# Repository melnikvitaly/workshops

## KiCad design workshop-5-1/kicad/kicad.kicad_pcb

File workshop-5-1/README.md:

# Workshop 5-1 — ESP32-S3 Dev Board

## 1. Task — Schematic of power supply

Design the power supply for the board: USB-C input, Li-Ion charging, battery
input, and a regulated 3.3 V rail for the ESP32-S3 module.

### Power chain

| Stage | Part | Function |
|-------|------|----------|
| USB-C input | `USB1` USB4105-GF-A-120 + `D4` 1N5819HW-7-F | 5 V bus input with reverse-current Schottky |
| Charger | `U5` BQ24040DSQR | Li-Ion linear charger, 5 V → `VBAT` |
| Battery | `CN1` XH-2AW | Single-cell Li-Ion connector on `VBAT` |
| Switch | `SW3` JS102011SAQN | Power switch on `VBAT` |
| Regulator | `U6` TLV75801PDBVR | Adjustable LDO, `VBAT` → `VCC` |

The LDO output is set by the `R9` / `R10` feedback divider. With
V<sub>FB</sub> = 0.55 V (TLV758P datasheet, eq. 2):

```
VOUT = VFB × (1 + R9 / R10) = 0.55 V × (1 + 255k / 51k) = 3.3 V
```

Charger programming and indication: `R7` (1 k) sets the fast-charge current,
`R6` (1 k) the pre-termination threshold, `R12` (10 k) the TS thermistor
branch. `LED1` shows charging (`CHG`), `LED2` shows USB power present (`PG`),
`LED3` shows the regulated rail is live.

### Schematic

Source file: [kicad/.history/kicad.kicad_sch](kicad/.history/kicad.kicad_sch)
(KiCad project: [kicad/kicad.kicad_pro](kicad/kicad.kicad_pro))

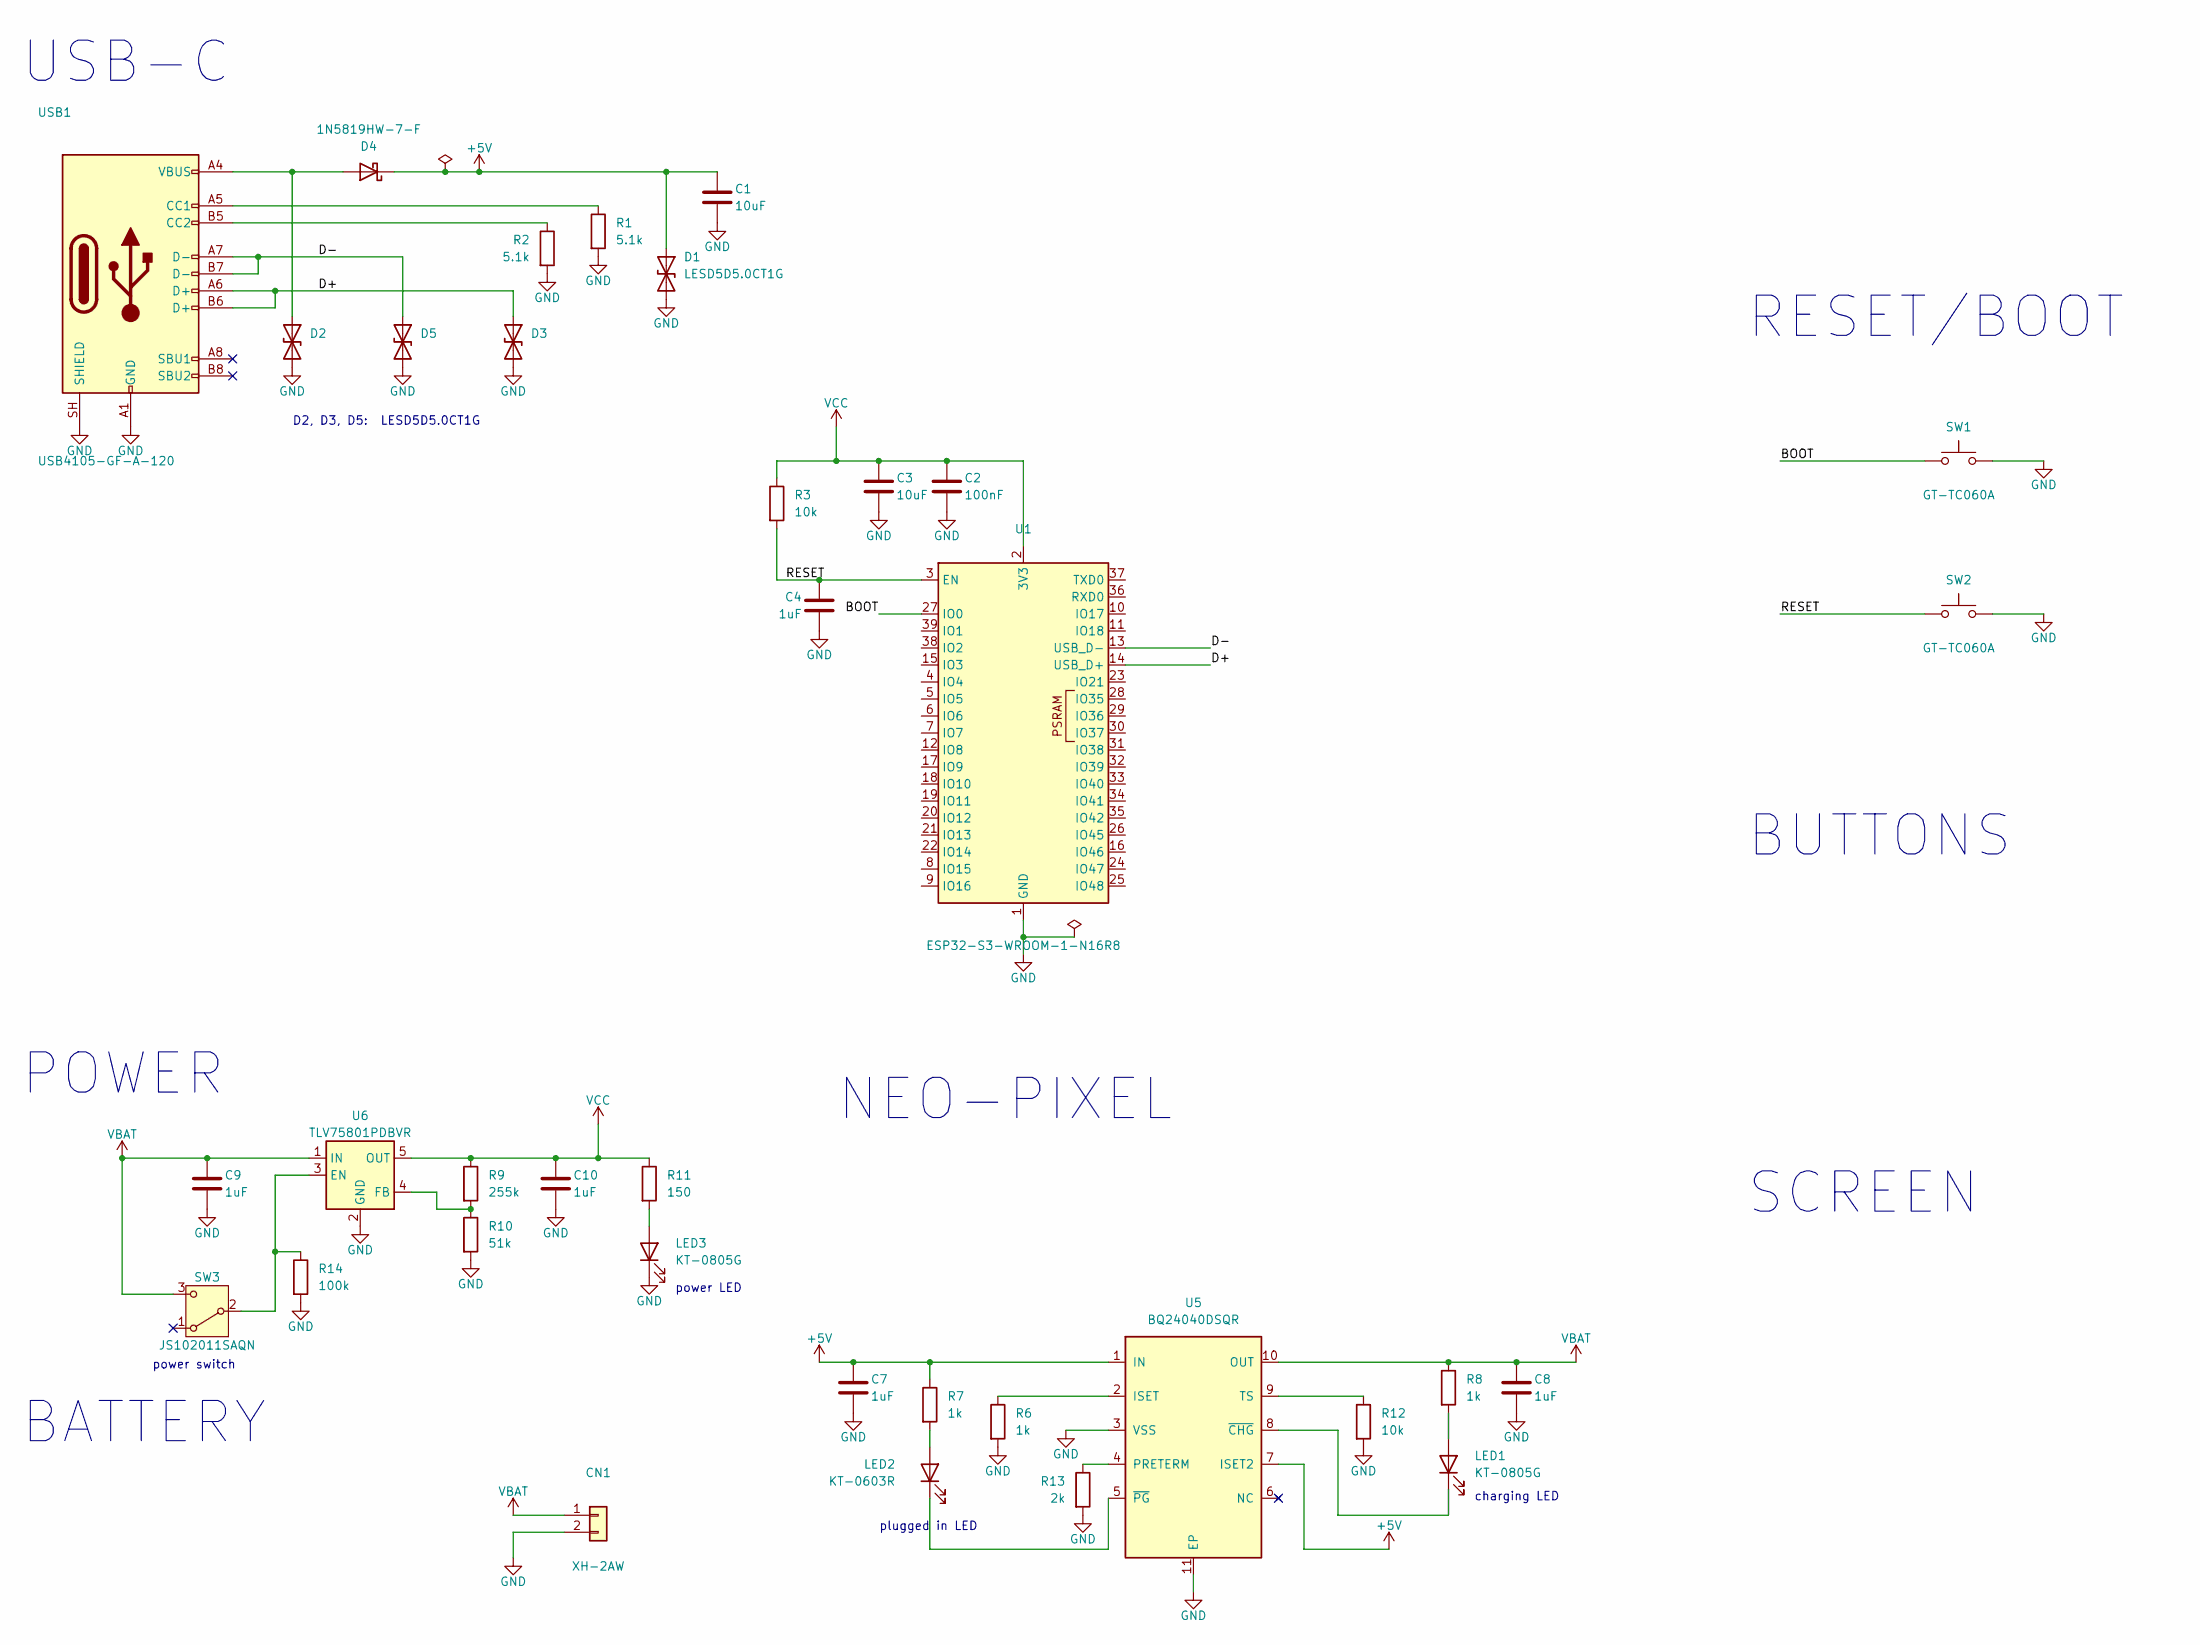
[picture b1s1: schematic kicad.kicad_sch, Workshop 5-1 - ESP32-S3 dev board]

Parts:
C1, C3: 10uF; C_0805_2012Metric
C2: 100nF; C_0402_1005Metric
C4, C7, C8, C9, C10: 1uF; C_0402_1005Metric
CN1: XH-2AW; JST_XH_B2B-XH-A_1x02_P2.50mm_Vertical
D1, D2, D3, D5: LESD5D5.0CT1G; D_SOD-523
D4: 1N5819HW-7-F; D_SOD-123
LED1, LED3: KT-0805G; LED_0805_2012Metric
LED2: KT-0603R; LED_0603_1608Metric
R1, R2: 5.1k; R_0402_1005Metric
R3, R12: 10k; R_0402_1005Metric
R6, R7, R8: 1k; R_0402_1005Metric
R9: 255k; R_0402_1005Metric
R10: 51k; R_0402_1005Metric
R11: 150; R_0402_1005Metric
R13: 2k; R_0402_1005Metric
R14: 100k; R_0402_1005Metric
SW1, SW2: GT-TC060A; SW_SPST_TL3342
SW3: JS102011SAQN; SW_SPDT_CK_JS102011SAQN
U1: ESP32-S3-WROOM-1-N16R8; ESP32-S3-WROOM-1
U5: BQ24040DSQR; WSON-10-1EP_2.5x2.5mm_P0.5mm_EP1.2x2mm
U6: TLV75801PDBVR; SOT-23-5
USB1: USB4105-GF-A-120; USB_C_Receptacle_GCT_USB4105-xx-A_16P_TopMnt_Horizontal

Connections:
/BOOT: SW1.1, U1.27 (IO0)
/D+: D3.1 (A1), U1.14 (USB_D+), USB1.A6 (D+), USB1.B6 (D+)
/D-: D5.1 (A1), U1.13 (USB_D-), USB1.A7 (D-), USB1.B7 (D-)
/RESET: C4.1, R3.2, SW2.1, U1.3 (EN)
unnamed: D2.1 (A1), D4.2 (A), USB1.A4 (VBUS), USB1.A9 (VBUS), USB1.B4 (VBUS), USB1.B9 (VBUS)
unnamed: LED1.2 (A), R8.2
unnamed: LED1.1 (K), U5.8 (~CHG)
unnamed: LED2.2 (A), R7.2
unnamed: LED2.1 (K), U5.5 (~PG)
unnamed: LED3.2 (A), R11.2
unnamed: R14.1, SW3.2 (B), U6.3 (EN)
unnamed: R6.1, U5.2 (ISET)
unnamed: R13.1, U5.4 (PRETERM)
unnamed: R12.1, U5.9 (TS)
unnamed: R9.2, R10.1, U6.4 (FB)
unnamed: R1.1, USB1.A5 (CC1)
unnamed: R2.1, USB1.B5 (CC2)
VBAT: C8.1, C9.1, CN1.1, R8.1, SW3.3 (C), U5.10 (OUT), U6.1 (IN)
VCC: C2.1, C3.1, C10.1, R3.1, R9.1, R11.1, U1.2 (3V3), U6.5 (OUT)

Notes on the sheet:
USB-C
D2, D3, D5: LESD5D5.0CT1G
RESET/BOOT
POWER
power switch
power LED
BATTERY
plugged in LED
charging LED
NEO-PIXEL
BUTTONS
SCREEN

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
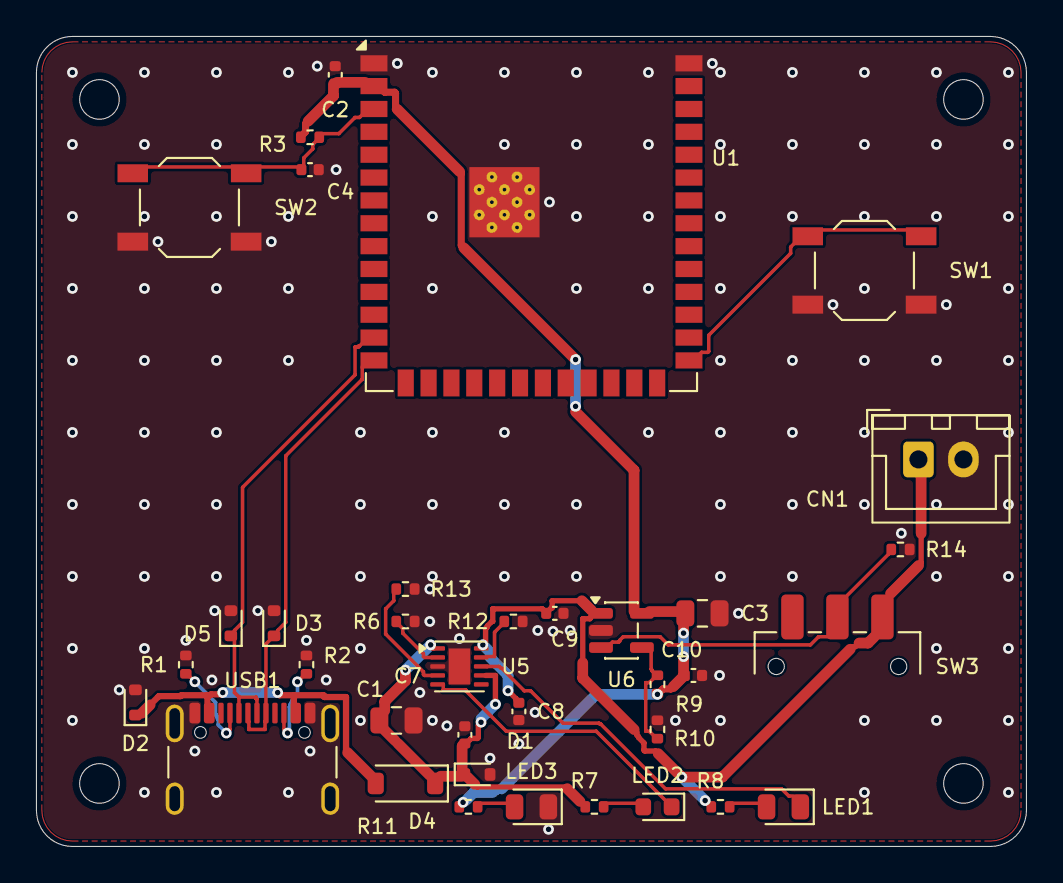
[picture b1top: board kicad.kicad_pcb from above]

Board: 2 copper layers, 55.0 x 45.0 mm, 36 parts (0 on the bottom side), 21 nets.

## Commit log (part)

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2026-04-05 homework-1-3-traffic-TrafficLights
2026-04-08 Homework-1-4
2026-04-10 hw 1-5
2026-04-10 hw-1-5
2026-04-10 hm-1-5
2026-04-11 HW-1-6
2026-04-17 mini-project
2026-04-17 uint8_t for pins
2026-04-18 LEDC lib for motor
2026-04-18 DebugOut=>Debug
2026-04-18 changeSpeed() to write to pins once
2026-04-18 Small fixes. Output fact sensor measurement frequency
2026-04-27 hw-2.1
2026-05-03 hw-2.2
2026-05-07 hw-2-3
2026-05-10 hw-2-4
2026-05-16 hw-2-5
2026-05-23 mp-2
2026-05-26 hw-3-1
2026-05-31 hw-3-2
2026-05-31 hw-3-3
2026-06-02 hw-3-4
2026-06-13 mp3 - wip
2026-06-13 mp3-wip
2026-06-13 mp-3-wip
2026-06-14 mp-3 remove currentTarget() from Input
2026-06-14 mp-3 fixes
2026-06-14 mp-3: add ema
2026-06-16 mp-3-afterreview. Encoder using pcnt
2026-06-16 mp-3: review what is IDF components
2026-06-25 workshop-4-2-wip
2026-06-25 workshop-4-1
